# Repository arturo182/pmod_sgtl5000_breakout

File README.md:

# SGTL5000 I2S Audio Codec PMOD

A simple breakout board for the SGTL5000 Audio Codec in PMOD format.

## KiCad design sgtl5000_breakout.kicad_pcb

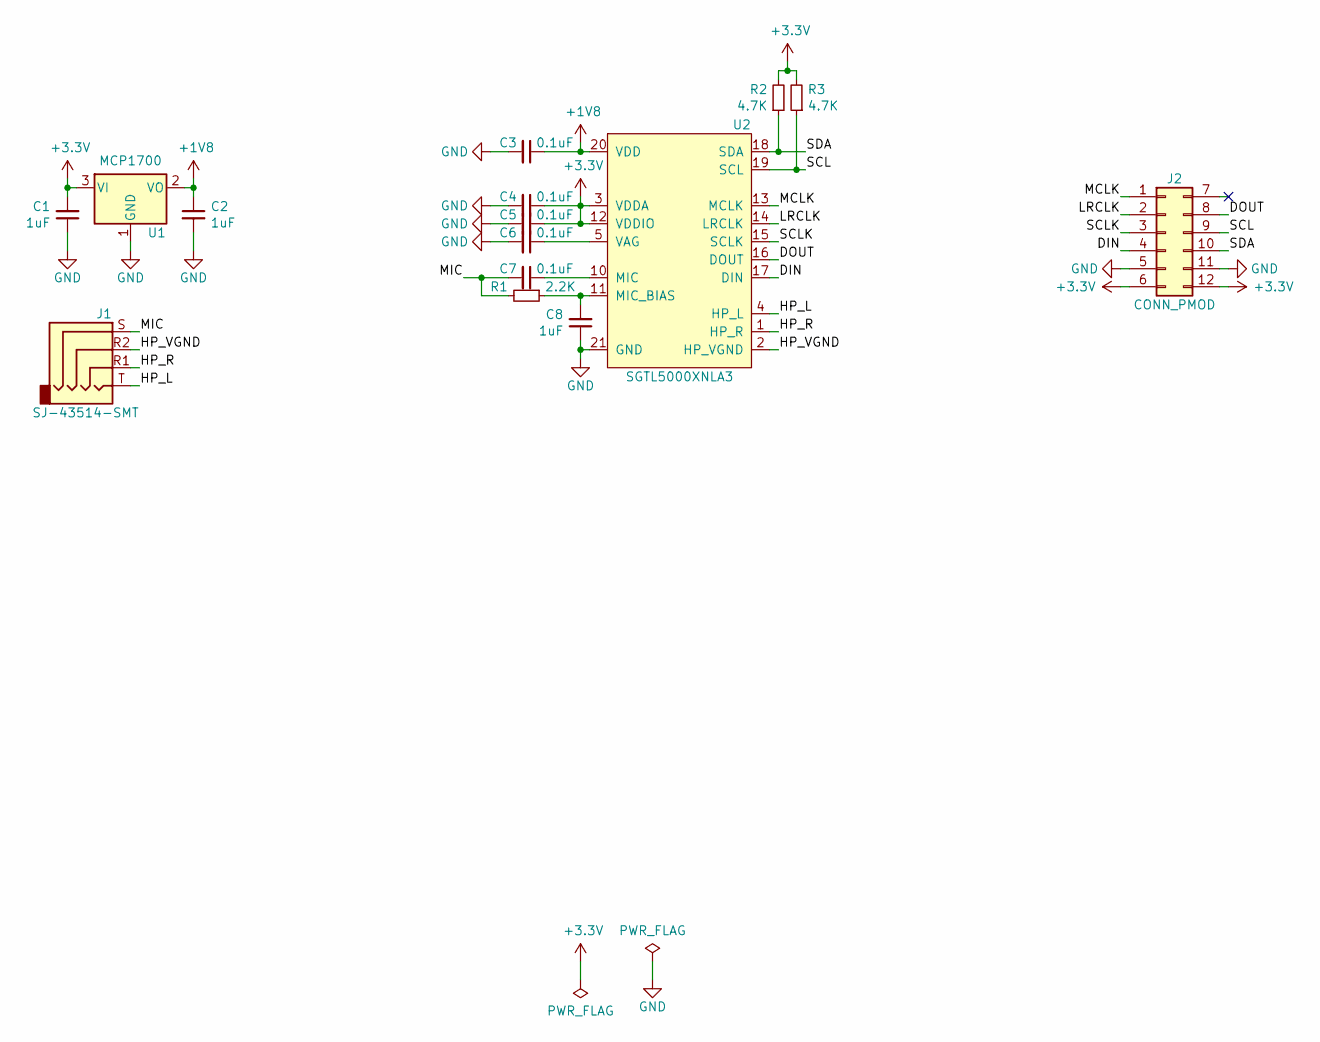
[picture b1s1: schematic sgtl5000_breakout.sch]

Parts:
C1, C2, C8: 1uF; C_0603_1608Metric
C3, C4, C5, C6, C7: 0.1uF; C_0603_1608Metric
J1: SJ-43514-SMT; Jack_3.5mm_CUI_SJ-43514-SMT_Horizontal
J2: CONN_PMOD; PMODHeader_2x06_P2.54mm_Horizontal
R1: 2.2K; R_0603_1608Metric
R2, R3: 4.7K; R_0603_1608Metric
U1: MCP1700; SOT-23
U2: SGTL5000XNLA3; QFN-20-1EP_3x3mm_P0.4mm_EP1.65x1.65mm

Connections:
+1V8: C2.1, C3.1, U1.2 (VO), U2.20 (VDD)
+3V3: C1.2, C4.1, C5.1, J2.6, J2.12, R2.2, R3.2, U1.3 (VI), U2.3 (VDDA), U2.12 (VDDIO)
/DIN: J2.4, U2.17 (DIN)
/DOUT: J2.8, U2.16 (DOUT)
/HP_L: J1.T, U2.4 (HP_L)
/HP_R: J1.R1, U2.1 (HP_R)
/HP_VGND: J1.R2, U2.2 (HP_VGND)
/LRCLK: J2.2, U2.14 (LRCLK)
/MCLK: J2.1, U2.13 (MCLK)
/MIC: C7.2, J1.S, R1.2
/SCL: J2.9, R3.1, U2.19 (SCL)
/SCLK: J2.3, U2.15 (SCLK)
/SDA: J2.10, R2.1, U2.18 (SDA)
GND: C1.1, C2.2, C3.2, C4.2, C5.2, C6.2, C8.1, J2.5, J2.11, U1.1 (GND), U2.21 (GND)
unnamed: C6.1, U2.5 (VAG)
unnamed: C7.1, U2.10 (MIC)
unnamed: C8.2, R1.1, U2.11 (MIC_BIAS)

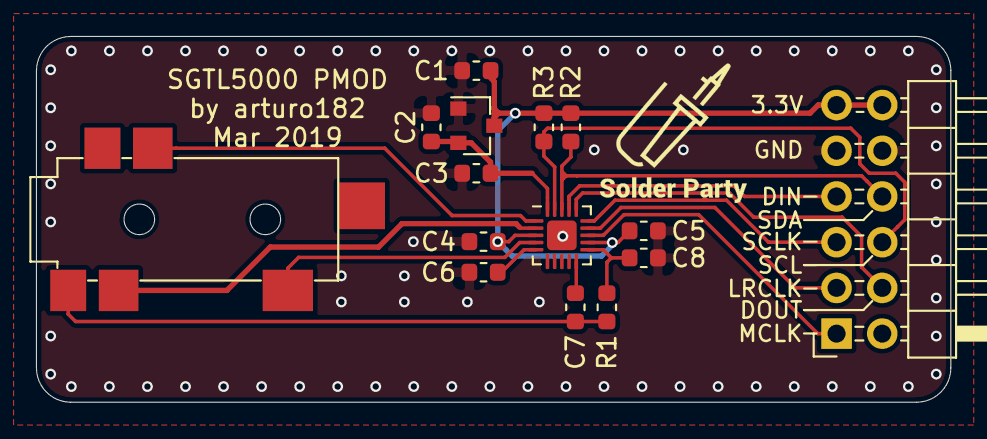
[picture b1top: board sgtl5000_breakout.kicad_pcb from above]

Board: 2 copper layers, 50.8 x 20.3 mm, 15 parts (0 on the bottom side), 17 nets.

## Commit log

2019-05-12 Initial import
